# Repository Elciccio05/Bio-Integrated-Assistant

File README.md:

# Bio-Integrator
A digital device, created to be fixed on your back and seamlessly integrate biological functions with technological capabilities

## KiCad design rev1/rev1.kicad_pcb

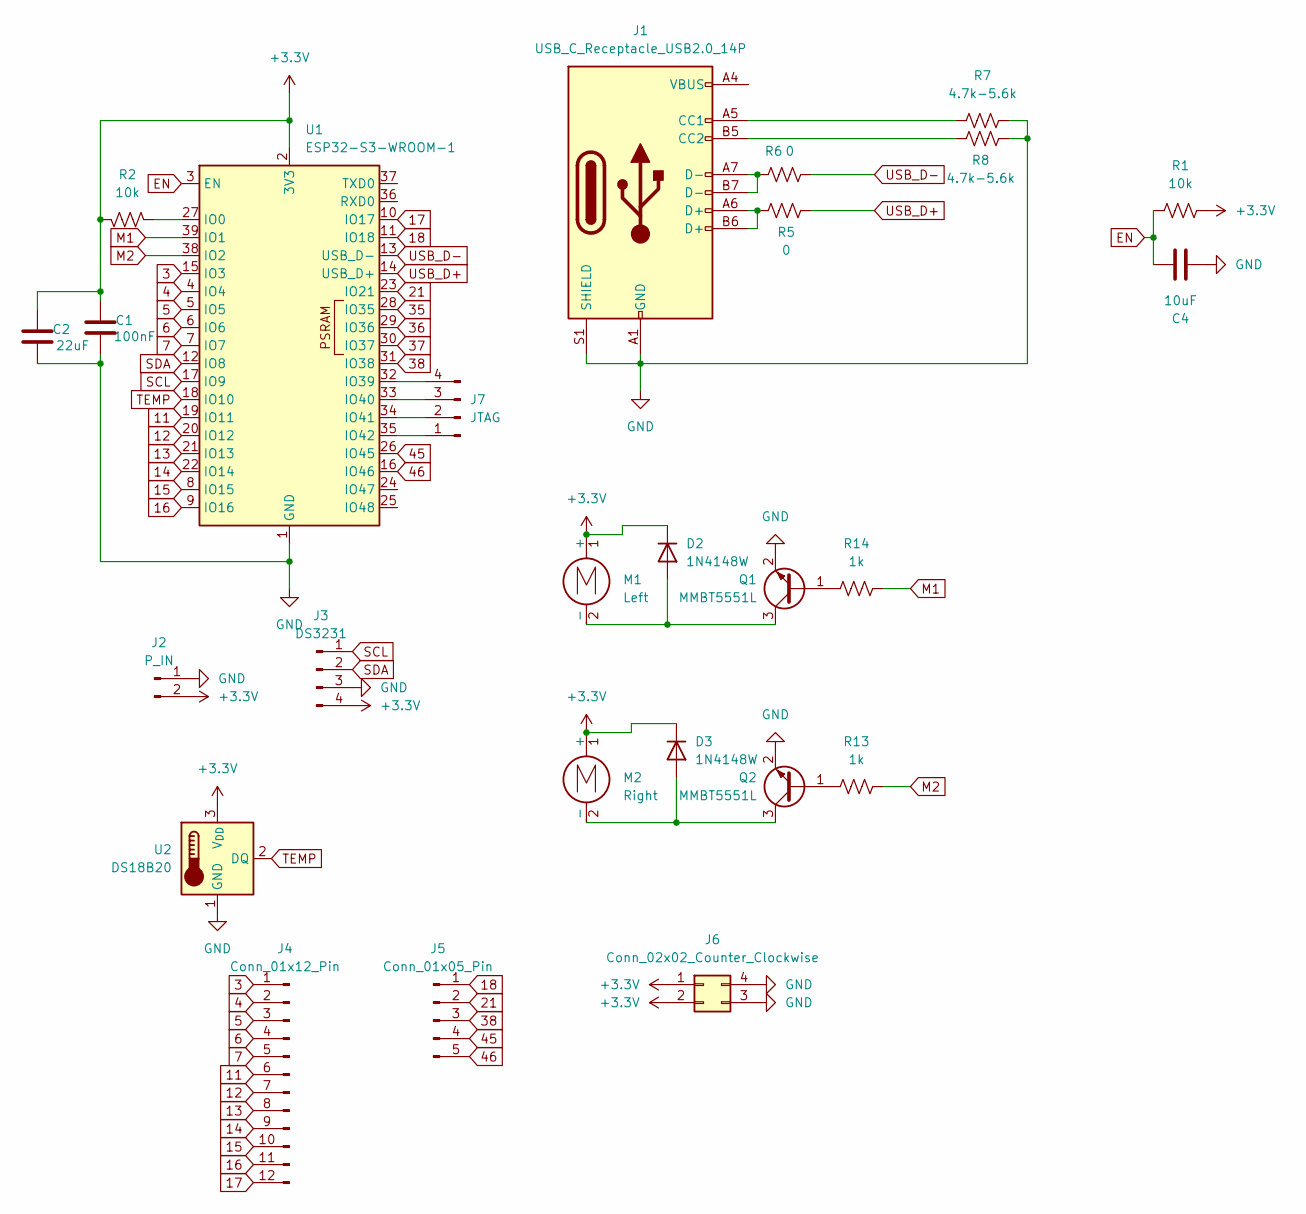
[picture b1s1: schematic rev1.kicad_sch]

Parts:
C1: 100nF; C_0603_1608Metric_Pad1.08x0.95mm_HandSolder
C2: 22uF; C_0603_1608Metric_Pad1.08x0.95mm_HandSolder
C4: 10uF; C_0603_1608Metric_Pad1.08x0.95mm_HandSolder
D2, D3: 1N4148W; D_SOD-123
J1: USB_C_Receptacle_USB2.0_14P; USB_C_Receptacle_GCT_USB4105-xx-A_16P_TopMnt_Horizontal
J2: P_IN; PinHeader_1x02_P2.54mm_Vertical
J3: DS3231; PinHeader_1x06_P2.54mm_Vertical
J4: Conn_01x12_Pin; PinHeader_1x12_P2.54mm_Vertical
J5: Conn_01x05_Pin; PinHeader_1x05_P2.54mm_Vertical
J6: Conn_02x02_Counter_Clockwise; PinHeader_2x02_P2.54mm_Vertical
J7: JTAG; PinHeader_1x04_P2.54mm_Vertical
M1: Left; PinHeader_1x02_P2.54mm_Vertical
M2: Right; PinHeader_1x02_P2.54mm_Vertical
Q1, Q2: MMBT5551L; SOT-23
R1, R2: 10k; R_0805_2012Metric_Pad1.20x1.40mm_HandSolder
R5, R6: 0; R_0805_2012Metric_Pad1.20x1.40mm_HandSolder
R7, R8: 4.7k-5.6k; R_0805_2012Metric_Pad1.20x1.40mm_HandSolder
R13, R14: 1k; R_0805_2012Metric_Pad1.20x1.40mm_HandSolder
U1: ESP32-S3-WROOM-1
U2: DS18B20; TO-92_Inline

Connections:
3: J4.1, U1.15 (IO3)
4: J4.2, U1.4 (IO4)
5: J4.3, U1.5 (IO5)
6: J4.4, U1.6 (IO6)
7: J4.5, U1.7 (IO7)
11: J4.6, U1.19 (IO11)
12: J4.7, U1.20 (IO12)
13: J4.8, U1.21 (IO13)
14: J4.9, U1.22 (IO14)
15: J4.10, U1.8 (IO15)
16: J4.11, U1.9 (IO16)
17: J4.12, U1.10 (IO17)
18: J5.1, U1.11 (IO18)
21: J5.2, U1.23 (IO21)
35: U1.28 (IO35)
36: U1.29 (IO36)
37: U1.30 (IO37)
38: J5.3, U1.31 (IO38)
45: J5.4, U1.26 (IO45)
46: J5.5, U1.16 (IO46)
+3.3V: C1.1, C2.1, D2.1 (K), D3.1 (K), J2.2, J3.4, J6.1, J6.2, M1.1 (+), M2.1 (+), R1.2, R2.2, U1.2 (3V3), U2.3 (V_{DD}); also elsewhere on the board
EN: C4.2, R1.1, U1.3 (EN)
GND: C1.2, C2.2, C4.1, J1.A1 (GND), J1.A12 (GND), J1.B1 (GND), J1.B12 (GND), J1.S1 (SHIELD), J2.1, J3.3, J6.3, J6.4, Q1.2 (E), Q2.2 (E), R7.2, R8.2, U1.1 (GND), U1.40 (GND), U1.41 (GND), U2.1 (GND)
M1: R14.2, U1.39 (IO1)
M2: R13.2, U1.38 (IO2)
unnamed: D2.2 (A), M1.2 (-), Q1.3 (C)
unnamed: D3.2 (A), M2.2 (-), Q2.3 (C)
unnamed: J1.A5 (CC1), R7.1
unnamed: J1.B5 (CC2), R8.1
unnamed: J1.A6 (D+), J1.B6 (D+), R5.2
unnamed: J1.A7 (D-), J1.B7 (D-), R6.2
unnamed: J1.A4 (VBUS), J1.A9 (VBUS), J1.B4 (VBUS), J1.B9 (VBUS)
unnamed 32: J7.1, U1.35 (IO42); also elsewhere on the board
unnamed 33: J7.2, U1.34 (IO41); also elsewhere on the board
unnamed 34: J7.3, U1.33 (IO40); also elsewhere on the board
unnamed 35: J7.4, U1.32 (IO39); also elsewhere on the board
unnamed: Q1.1 (B), R14.1
unnamed: Q2.1 (B), R13.1
unnamed: R2.1, U1.27 (IO0)
SCL: J3.1, U1.17 (IO9)
SDA: J3.2, U1.12 (IO8)
TEMP: U1.18 (IO10), U2.2 (DQ)
USB_D+: R5.1, U1.14 (USB_D+)
USB_D-: R6.1, U1.13 (USB_D-)

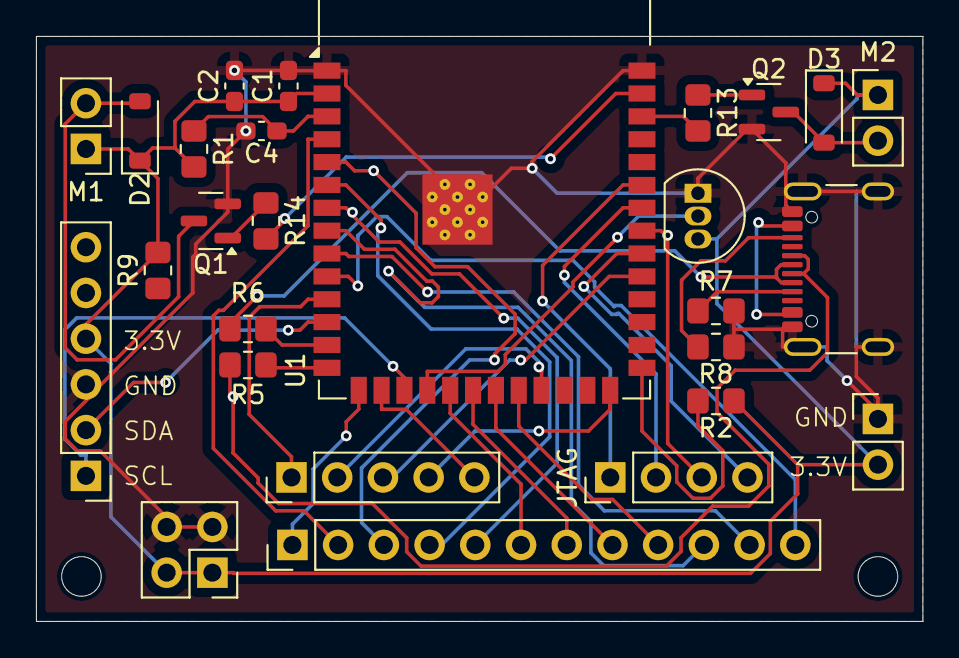
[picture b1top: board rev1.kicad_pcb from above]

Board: 2 copper layers, 49.2 x 32.5 mm, 27 parts (0 on the bottom side), 41 nets.

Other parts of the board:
JTAG: JTAG; PinHeader_1x04_P2.54mm_Vertical
R9: 10k; R_0805_2012Metric_Pad1.20x1.40mm_HandSolder

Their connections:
+3.3V: R9.2; also elsewhere on the board
unnamed 32: JTAG.1; also elsewhere on the board
unnamed 33: JTAG.2; also elsewhere on the board
unnamed 34: JTAG.3; also elsewhere on the board
unnamed 35: JTAG.4; also elsewhere on the board

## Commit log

2025-07-10 Schematic and PCB projects
    Made with KiCad 9.0
2025-07-10 Custom KiCad Libraries
2025-07-11 Schematic and PCB project
    Made with KiCad 9.0
2025-07-12 ESP32 code
    Wrote using VS Code and PlatformIO
2025-07-13 Exploded view of the physical device
    Made with Fusion360
2025-07-13 Fusion360 project
